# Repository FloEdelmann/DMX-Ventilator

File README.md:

# DMX-Ventilator

## Motivation

Wir waren im Dezember 2015 auf dem [Contact Indoor Festival München](https://www.facebook.com/events/544198745721461/ "Facebook-Versnataltung"). Was uns dort neben der Musik am meisten beeindruckt hat, waren die Ventilatoren, die als Effektgeräte hinter der Bühne im Zenith&nbsp;I heruntergelassen werden und sich drehen konnten. Die Flügel haben in einer einstellbaren Farbe geleuchtet und auch die Geschwindigkeit war in einem weiten Bereich regelbar.

Auf YouTube gibt es sie auch in Bewegung zu sehen:
https://www.youtube.com/watch?v=OpufAzwtyVI (rot in verschiedenen Geschwindigkeiten)
https://www.youtube.com/watch?v=SzctCUNd09I (blau)

So etwas wollten wir jetzt auch auch!

## Planung

### Elektronik

Bei der Suche nach DMX-Selbstbau-Projekten verweist letztendlich fast jede Quelle auf [Hendrik Hölschers Seiten](http://www.hoelscher-hi.de/hendrik/wahl.htm). Sein [DMX-LED-Dimmer](http://www.hoelscher-hi.de/hendrik/light/dmxled.htm) hat schon einige Features, die auch unser Ventilator haben soll: Über DMX können 8 Kanäle gesteuert werden (zusätzlich sogar gestrobed), dank AVR-Microcontroller ist die Schaltung einfach zu programmieren und zu verändern und die Hardware ist sehr modular gehalten, sodass auch andere Projekte einfach realisiert werden können.

Es fehlt jedoch die Ansteuerung eines Motors. Außerdem wollen wir LED-Strips verwenden, da sie einfach zu montieren sind, und die brauchen noch eine extra Stromversorgung. Also muss eine zweite Platine her, die die Ansteuerungen übernimmt. Sie ist so gelayoutet, dass auch ein Lochraster-Aufbau möglich ist.

Beide Schaltungen hängen dann zusammen an einer 12V-<abbr title="Gleichspannung">DC</abbr>-Stromversorgung und werden über die 8-polige Steckerleiste miteinander verbunden.

Zum Programmieren des Microcontrollers werden über den ISP-Port die nötigen Anschlüsse herausgeführt. Da es jedoch ein standardisiertes 10-Pin-ISP-Interface gibt, das auch die gängigen [Programmieradapter](http://www.mikrocontroller.net/articles/AVR_In_System_Programmer) verwenden, habe ich mir ein zusätzliches Adapterkabel gebaut.

**Downloads für [EAGLE](http://www.cadsoft.de/download-eagle/):** [avr-adapter.sch](eagle/avr-adapter.sch), [dmx-transciever.sch](eagle/dmx-transciever.sch), [motortreiber.brd](eagle/motortreiber.brd), [motortreiber.sch](eagle/motortreiber.sch)

### Gehäuse & Mechanik

Am Motor wird eine Edelstahlwelle befestigt, die von einem Kugellager drehbar in Position gehalten wird. Die Rotorblätter sollen aus milchigem Plexiglas geschnitten werden, da diese als Lichtleiter bei der Anstrahlung mit den LED-Strips hoffentlich eine gute Ausleuchtung erzielen. Sie werden zwischen zwei großen Beilagscheiben mit mehreren Schrauben / Nieten befestigt und als ganzes von vorne an die Achse geschraubt.

Mit [Autodesk 123D Design](http://www.123dapp.com/design) lässt sich recht schnell ein vorzeigbares 3D-Modell erstellen. Dabei kann man schon vor dem physischen Aufbau Mängel in der Konstruktion erkennen und beheben.

### Teile- und Bestellliste

| Stück | Bezeichnung                    | Link |
| -----:| ------------------------------ | ---- |
| 1 | 12V-DC-Getriebemotor 200rpm        | [eBay](http://www.ebay.de/itm/351368945189) |
| 1 | Neuer Motor                        | [Conrad](https://www.conrad.de/de/getriebemotor-12-v-modelcraft-rb350030-0a101r-130-227544.html) |
| 1 | RGB-LED-Strip 4m                   | [eBay](http://www.ebay.de/itm/151160889546) |
| 1 | 12V-DC-Netzteil 4A                 | [eBay](http://www.ebay.de/itm/151581215241) |
| 1 | Lochrasterplatine 4×6cm            | [eBay](http://www.ebay.de/itm/261846070281) |
| 1 | Transciever-Board                  | [embedded projects](http://shop.embedded-projects.net/sonstige/dmx-transceiver.html) |
| 1 | 3-Pol-XLR-Einbaubuchse (DMX-In)    | [Pollin](http://www.pollin.de/shop/dt/NTM2OTQ1OTk-/HiFi_Car_HiFi_Video_TV/Steckverbinder/Sonstiges/XLR_Einbaubuchse.html) |
| 1 | 3-Pol-XLR-Einbaustecker (DMX-Out)  | [Pollin](http://www.pollin.de/shop/dt/NDM2OTQ1OTk-/HiFi_Car_HiFi_Video_TV/Steckverbinder/Sonstiges/XLR_Einbaustecker.html) |
|   | mehradriges Kabel (z.B. IDE-Kabel) | |
| 1 | Edelstahlwelle 50mm, ø 20mm        | [eBay](http://www.ebay.de/itm/121103784726) |
| 1 | Flanschlager ø 20mm                | [eBay](http://www.ebay.de/itm/251852780407) |
|   | Acrylglas, 6mm                     | [eBay](http://www.ebay.de/itm/151269316675) |
|   | Aluminium-Platte, 4mm              | [eBay](http://www.ebay.de/itm/141345316955) |
|   | Holz (Multiplex), 16mm             | |
|   | MDF, 4mm                           | |
|   | Senkkopf-Holzschrauben             | |
| 6 | Rundkopf-Holzschrauben             | |
| 1 | Madenschraube M4                   | |
| 1 | Metallschraube M8, 35mm            | |
| 2 | Metallschraube M10, 30mm           | |
| 2 | Mutter M10                         | |
| 4 | Senkkopf-Metallschraube M2.5, 10mm | |
| 3 | Abstandshalter ca. 5mm             | |
| 3 | Abstandshalter ca. 12mm            | |

**Bestückung**

| Stück | Bezeichnung   | Teilenamen Transciever / Motortreiber | Link |
| -----:| ------------- | ------------------------------------- | ---- |
| 1 | 10-Pol-DIP-Switch | SW1 / –                | [eBay](http://www.ebay.de/itm/121855976441) |
| 1 | ATmega8515-P      | IC1 / –                | [eBay](http://www.ebay.de/itm/310716403642) |
| 1 | 75176AP           | IC2 / –                | [eBay](http://www.ebay.de/itm/381374573295) |
| 1 | 7805              | IC3 / –                | [Pollin](http://www.pollin.de/shop/dt/ODU5OTI4OTk-/Bauelemente_Bauteile/Aktive_Bauelemente/Spannungsregler/Spannungsregler_ST_L7805CV.html) |
| 1 | IC-Sockel 40-polig | für IC1 / –            | [Pollin](http://www.pollin.de/shop/dt/OTY5OTk1OTk-/Bauelemente_Bauteile/Mechanische_Bauelemente/IC_Fassungen_Adapterplatinen/IC_Fassung_40_polig.html) |
| 1 | IC-Sockel 8-polig | für IC2 / –            | [Pollin](http://www.pollin.de/shop/dt/Nzc5OTk1OTk-/Bauelemente_Bauteile/Mechanische_Bauelemente/IC_Fassungen_Adapterplatinen/IC_Praezisionsfassung_8_polig.html) |
| 3 | TLE-4202-B        | – / IC1, IC2, IC3      | [Pollin](http://www.pollin.de/shop/dt/NTU5ODk4OTk-/Bauelemente_Bauteile/Aktive_Bauelemente/IC/TLE4202B_STS_B57928.html) |
| 1 | Quartz 8MHz       | Q1 / –                 | [Pollin](http://www.pollin.de/shop/dt/MTk5OTY3OTk-/Bauelemente_Bauteile/Passive_Bauelemente/Quarze_Oszillatoren/Quarz.html) |
| 2 | Kondensator 27pF<br />(**genau!**) | C1, C2 / – | [Conrad](https://www.conrad.de/de/keramik-scheibenkondensator-27-pf-100-vdc-5-x-h-35-mm-x-4-mm-1-st-457175.html) |
| 2 | Kondensator 100nF | C7 / C4                | [Pollin](http://www.pollin.de/shop/dt/OTA4OTk3OTk-/Bauelemente_Bauteile/Passive_Bauelemente/Kondensatoren/Folien_Kondensator_100_nF.html) |
| 5 | Kondensator 220nF | – / C1, C2, C3, C6, C7 | [Pollin](http://www.pollin.de/shop/dt/OTgzOTk3OTk-/Bauelemente_Bauteile/Passive_Bauelemente/Kondensatoren/MKT_Kondensator.html) |
| 3 | Elko 100µF        | C5, C6 / C5            | [Pollin](http://www.pollin.de/shop/dt/MTM2OTg3OTk-/Bauelemente_Bauteile/Passive_Bauelemente/Elkos_Goldcaps/Elko_100_F_25_V_10_Stueck_NIPPON_CHEMI_CON_KZE.html) |
| 1 | LED rot 3mm       | LED1 / –               | [Pollin](http://www.pollin.de/shop/dt/MjY5OTc4OTk-/Bauelemente_Bauteile/Aktive_Bauelemente/LEDs/LED.html) |
| 1 | LED grün 3mm      | LED2 / –               | [Pollin](http://www.pollin.de/shop/dt/OTA5ODc4OTk-/Bauelemente_Bauteile/Aktive_Bauelemente/LEDs/LED_KINGBRIGHT_L_934SGDLK_gruen_3_mm_10_Stueck.html) |
| 1 | Poti 10kΩ         | R1 / –                 | [Pollin](http://www.pollin.de/shop/dt/MTM3OTU3OTk-/Bauelemente_Bauteile/Passive_Bauelemente/Potis_Trimmer_Encoder/Potentiometer_PIHER_PT_10.html) |
| 2 | Widerstand 1Ω<br />(4,7Ω geht auch) | – / R1, R2 | [Pollin](http://www.pollin.de/shop/dt/MTQyOTc3OTk-/Bauelemente_Bauteile/Passive_Bauelemente/Widerstaende/Metallfilm_Widerstaende.html) |
| 3 | Widerstand 390Ω<br />(470Ω geht auch) | R2, R3, R4 / – | [Pollin](http://www.pollin.de/shop/dt/ODIyOTc3OTk-/Bauelemente_Bauteile/Passive_Bauelemente/Widerstaende/Metallfilm_Widerstaende.html) |
| 1 | Stiftleiste 1×2   | JP4 / –                | [Pollin](http://www.pollin.de/shop/dt/OTQ0ODQ1OTk-/Bauelemente_Bauteile/Mechanische_Bauelemente/Steckverbinder_Klemmen/Stiftleiste_vergoldet_1x_20_polig_10_Stueck.html) (rowspan=5) |
| 2 | Stiftleiste 1×3   | JP2, JP3 / –           | |
| 1 | Stiftleiste 1×4   | – / JP2                | |
| 1 | Stiftleiste 1×5   | JP1 / –                | |
| 2 | Stiftleiste 1×8   | JP6 / JP1              | |
| 1 | Stiftleiste 2×3   | JP5 / –                | [Pollin](http://www.pollin.de/shop/dt/NDkyOTQ1OTk-/Bauelemente_Bauteile/Mechanische_Bauelemente/Steckverbinder_Klemmen/Stiftleiste.html) |
| 1 | Stiftbuchse 1×3   |                        | [Conrad](https://www.conrad.de/de/buchsenleiste-praezision-anzahl-reihen-1-polzahl-je-reihe-36-w-p-products-153-036-1-50-10-1-st-736427.html) (rowspan=4) |
| 1 | Stiftbuchse 1×4   |                        | |
| 1 | Stiftbuchse 1×2   |                        | |
| 2 | Stiftbuchse 1×8   |                        | |

## Aufbau der Elektronik

## TODO: Verbindungskabel falsch rum

## Programmieren

Der folgende Abschnitt bezieht sich auf das Programmieren unter Ubuntu Linux. Bei anderen Betriebssystemen müssen entsprechend andere Programme zum Assemblieren und Übertragen des Codes verwendet werden.

Als Programmier-Interface verwende ich [USBasp](http://www.fischl.de/usbasp/), das es als fertige Platine oder als Bausatz zum Selberlöten gibt. Nach Anschluss des Programmieradapters (siehe Foto oben) kann mit dem folgenden Befehl das Testfile von Hendrik Hölschers Webseite ([board.hex](http://www.hoelscher-hi.de/hendrik/light/ressources/board.hex)) übertragen werden:

    sudo avrdude -p atmega8515 -c usbasp -B 3 -U flash:w:board.hex

* `sudo`: ohne Root-Rechte bekomme ich eine Fehlermeldung (*access denied*)
* `-p atmega8515`: Angabe des verwendeten Microcontrollers
* `-c usbasp`: Angabe des Programmier-Interfaces
* `-B 3`: kleinster Wert für die `bit clock period`, damit USBasp erkannt wird
* `-U flash:w:board.hex`: schreibe das Testfile in den Flash-Speicher

**Testfunktionen:**

| DIP-Switch    | Bedeutung |
| ------------- | --------- |
| Alle DIPs off | Blinken der roten LED zeigt an, dass das Testfile in den Flash geladen wurde. |
| Alle DIPs an  | Leuchten der grünen LED zeigt an, dass alle DIP-Schalter korrekt verlötet sind. |
| DIP1 an       | Leuchten der grünen LED zeigt an, dass die fuse bits angepasst wurden. |
| DIP2 an       | Leuchtet die grüne LED, liegt ein korrektes DMX-Signal an. Ein Blinken indiziert, dass D+ und D- verpolt sind. |
| DIP3 an       | Leuchtet die grüne LED, funktioniert die angeschlossene ZC-Detection. (für uns irrelevant) |

Mit dem Testprogramm habe ich festgestellt, dass alles passt, aber die Fuse bits noch nicht gesetzt wurden. Zuerst wollen wir die aktuell gesetzten Bits lesen: `sudo avrdude -p atmega8515 -c usbasp -B 3 -n` liefert `Fuses OK (E:FF, H:D9, L:E1)`. Durch Herumspielen mit dem [AVR Fuse Calculator](http://www.engbedded.com/fusecalc), bis die Werte mit denen in http://www.hoelscher-hi.de/hendrik/light/ressources/an011.pdf übereinstimmen, bin ich auf den folgenden Befehl gekommen:

    sudo avrdude -p atmega8515 -c usbasp -B 3 -U lfuse:w:0x3f:m -U hfuse:w:0x9d:m

Danach lief das Testprogramm problemlos durch.

### `udev`-Regel

Um `avrdude` nicht jedes Mal mit Root-Rechten ausführen zu müssen, fügt man eine neue *udev rule* hinzu. Dazu erstellt man die Datei `/etc/udev/rules.d/60-usbasp.rules` mit dem folgenden Inhalt:

    # USBasp
    SUBSYSTEM=="usb", ATTRS{idVendor}=="16c0", ATTRS{idProduct}=="05dc", GROUP="adm", MODE="0666"

Danach wird die neue Datei mit `sudo service udev restart` eingelesen und man kann künftig `avrdude` ohne Root-Rechte zum Übertragen verwenden.

### Assembler und Makefile

Danach geht es an den eigentlichen Projekt-Code (`LED.asm` inkl. `lib_asm.asm`).

Als Assembler (der `.asm`-Dateien in übertragbare `.hex`-Dateien assembliert) verwenden wir `avra`.

Damit wir zum Assemblieren und Übertragen nicht immer zwei einzelne Befehle ausführen müssen, erstellen wir uns ein **Makefile**:

    file = LED.hex

    all: $(file)
        avrdude -p atmega8515 -c usbasp -B 3 -U flash:w:$(file)

    %.hex: %.asm
        avra -I "/usr/share/avra" $*.asm

    fuse:
        avrdude -p atmega8515 -c usbasp -B 3 -U lfuse:w:0x3f:m -U hfuse:w:0x9d:m

    test:
        avrdude -p atmega8515 -c usbasp -B 3 -U flash:w:board.hex

**Achtung:** Die Einrückung muss hier mit Tabs geschehen!

In `/usr/share/avra` liegen die Microcontroller-Definitionsdateien, also insbesondere auch `m8515def.inc`, das wir für unser Projekt brauchen. Mit der Option `-I` weisen wir `avra` an, auch in diesem Verzeichnis nach den Include-Dateien zu suchen.

Beim ersten Ausführen mit `make` gab es Fehlermeldungen, dass `avra` diese Kommentare nicht kennt: `/* … */` und `// …`. Daher habe ich sie durch `; …` ersetzt. Danach konnte ich bereits ohne Probleme assemblieren und übertragen und das Programm funktioniert tadellos.

Danach habe ich die beiden Dateien zusammengeführt, um leichter zu verstehen, was wo passiert.

Jetzt kann es an die eigenen Erweiterungen gehen!

### DIP-Switch

Die DIP-Schalter-Stellungen sollen unverändert weiterhin gelten:
**DIP1 - DIP9** stellen die DMX-Adresse dar (Bit 0 - 8 in aufsteigender Reihenfolge)
**DIP10** aktiviert den Standalone Mode, womit folgendes gilt:

| DIP-Switch | Funktion        |
| ----------:| --------------- |
|      1 - 3 | Programm        |
|      5 - 8 | Geschwindigkeit |
|          9 | Strobe          |

Die auswählbaren Programme müssen aber entsprechend angepasst bzw. durch neue ersetzt werden, damit diese die verschiedenen LED-Farben und den Motor entsprechend ansteuern. Zum Testen reichen aber erst mal die vorgegebenen.

### Standalone-Programme

Ich habe den IC2 (75176B), welcher für die Übersetzung von DMX in das vom Microcontroller verständliche USART zuständig ist, in China bestellt. Da dieser wegen der langen Lieferzeit noch nicht da ist, mache ich mich zuerst an die Standalone-Programme. Diese werden durch den [DIP-Switch](#dip-switch) bestimmt und können daher ohne anliegendes DMX-Signal getestet werden.

Ein vorgegebenes Programm (DIP2 an) sieht z.B. so aus:

    .org PAT1                   ; Lauflicht
    .dw 0b0000000001
    .dw 0b0000000010
    .dw 0b0000000100
    .dw 0b0000001000
    .dw 0b0000010000
    .dw 0b0000100000
    .dw 0b0001000000
    .dw 0b0010000000
    .dw 0b1100000000

Dabei stehen die einzelnen Zeilen für die unterschiedlichen Zustände, die ineinander übergefaded werden sollen. Das erste Bit ist nur beim letzten Zustand gesetzt, um das Ende des Programms zu kennzeichnen. Danach folgen die Werte für die Ausgänge `A` (ungenutzt), `M+`, `M-`, `R`, `G`, `B`, `P` (ungenutzt, aber aufs zweite Board herausgeführt) sowie zwei weitere nicht benutzte Ausgänge.

Der Motor dreht sich im Uhrzeigersinn, wenn `M+` und `M-` auf `0` und `1` gesetzt werden bzw. gegen den Uhrzeigersinn für `1` und `0`. Liegt an beiden Ausgängen der selbe Pegel an, dreht der Motor sich nicht.

Die LEDs sind an, wenn der entsprechende Ausgang auf *low* gesetzt wird.

Das folgende Beispiel zeigt also einen RGB-Fader, bei dem der Motor immer im Uhrzeigersinn dreht:

<pre>
.dw 0b0<span style="color:#aaa">0</span><span style="color:#d80">01</span><span style="color:red">0</span>11<span style="color:#aaa">000</span>
.dw 0b0<span style="color:#aaa">0</span><span style="color:#d80">01</span><span style="color:red">0</span><span style="color:#0c0">0</span>1<span style="color:#aaa">000</span>
.dw 0b0<span style="color:#aaa">0</span><span style="color:#d80">01</span>1<span style="color:#0c0">0</span>1<span style="color:#aaa">000</span>
.dw 0b0<span style="color:#aaa">0</span><span style="color:#d80">01</span>1<span style="color:#0c0">0</span><span style="color:#00f">0</span><span style="color:#aaa">000</span>
.dw 0b0<span style="color:#aaa">0</span><span style="color:#d80">01</span>11<span style="color:#00f">0</span><span style="color:#aaa">000</span>
.dw 0b<strong>1</strong><span style="color:#aaa">0</span><span style="color:#d80">01</span><span style="color:red">0</span>1<span style="color:#00f">0</span><span style="color:#aaa">000</span>
</pre>

Die anderen Programme könnt ihr im Code selbst anschauen.

### DMX-Channels

Die DMX-Channels sollen wie folgt aussehen:

| DMX-Channel | Funktion                              |
| -----------:| ------------------------------------------------------------------------ |
|           0 | <p>Motor</p><table><tbody><tr><td align="right">0 - 3</td><td>aus</td></tr><tr><td align="right">4 - 119</td><td>gegen den Uhrzeigersinn (immer langsamer)</td></tr><tr><td align="right">120 - 139</td><td>aus (Mitte)</td></tr><tr><td align="right">140 - 255</td><td>im Uhrzeigersinn (immer schneller)</td></tr></tbody></table> |
|           1 | rote LEDs                             |
|           2 | grüne LEDs                            |
|           3 | blaue LEDs                            |
|           4 | LED-Strobe (optional)                 |
|           5 | Master-Helligkeit für LEDs (optional) |

Mehr Channels brauchen wir nicht.

Um die Farb-Channels schon einmal richtig zu mappen, habe ich im Label `pwm_exit` den Abschnitt angepasst, der die Werte vom `DMX_FIELD` auf das `PWM_FIELD` kopiert, von wo aus sie im nächsten Timer-Durchlauf ausgegeben werden.

Der Motor erfordert etwas mehr Aufwand, da von einem Channel aus zwei Ausgänge gesteuert werden sollen. Ich habe mir die Funktion `eval_strobe_freq` zum Vorbild genommen und auch von der main loop aus die neue Funktion `eval_motor_speed` aufgerufen. Diese springt je nach DMX-Wert in verschiedene Sublabels. Von dort aus wird der DMX-Wert auf einen Bereich von 0 bis 115 gebracht und mit diesem Wert aus `MOTOR_MAP` der jeweils auszugebene PWM-Wert (0 bis 255) geholt und ins `PWM_FIELD` geschrieben. Das ist nötig, da wir leider nicht einfach mit einer Fließkommazahl multiplizieren können (etwa `y = x * 255/115;`).

Die Strobe-Funktion war ja schon eingebaut und musste nur so angepasst werden, dass sie auf DMX-Kanal 4 statt 1 hört (einfach) und nur die LEDs und nicht den Motor flasht. Dazu habe ich im Label `pwm` den Code so geändert, dass alle Kanäle immer normal auf den jeweiligen Wert, und danach beim Blackout mit Hilfe eines logischen Oders nur die LED-Kanäle auf 1 gesetzt werden.

#### Motor-Bremse

Da der Motor nicht allzu schnell von einem Wert auf einen anderen beschleunigen bzw. abbremsen sollte, habe ich die Funktion `eval_motor_speed` danach so abgeändert, dass in jedem Durchlauf der Soll-Wert (`DMX_FIELD` und `MOTOR_MAP`) und der Ist-Wert (`PWM_FIELD`) verglichen werden und der Output nur um eins inkrementiert oder dekrementiert wird.

Da das aber viel zu schnell abläuft, vergleiche ich vorher zusätzlich, dass die beiden Register `checkMotorL` und `checkMotorH` gleich null sind. Dieses Quasi-16-bit-Register wird vom Interrupt-Handler `pwm`, der bei jedem Overflow von `Timer0` aufgerufen wird, je um eins inkrementiert. Das war dann aber wiederum viel zu langsam, sodass `checkMotorH` sofort wieder auf null zurückgesetzt wird, sobald es den Wert 20 erreicht hat. Die Geschwindigkeit sieht im Testbetrieb vernünftig aus, eventuell muss an dem Wert aber noch gefeilt werden, sobald der Motor eingebaut ist.

Leider hat es unseren ersten Motor mit dem Wert von 20 zerschossen. Wir haben danach einen leistungsfähigeren besorgt, trotzdem wollten wir auf Nummer sicher gehen und haben den Wert auf 40 verdoppelt. Da dann aber das Anfahren sehr, sehr langsam ist, erlauben wir ein Inkrementieren öfter als ein Dekrementieren.

### Hilfe bei Assembler-Kommandos

Da man häufig mal nachschauen muss, was die einzelnen Assembler-Kommandos bedeuten, habe ich hier eine kleine Hilfe programmiert: Einfach Befehl oder Direktive eingeben (z.B. `jmp` oder `.equ`) und es werden Einzelheiten angezeigt.

<input type="text" id="asm-help-input" placeholder="Assembler-Hilfe" />
<div id="asm-help-output"></div>
<script type="text/javascript" src="asm-help.js"></script>

## Mechanischer Aufbau

*(readme is not complete; see rest of the repository for more information)*

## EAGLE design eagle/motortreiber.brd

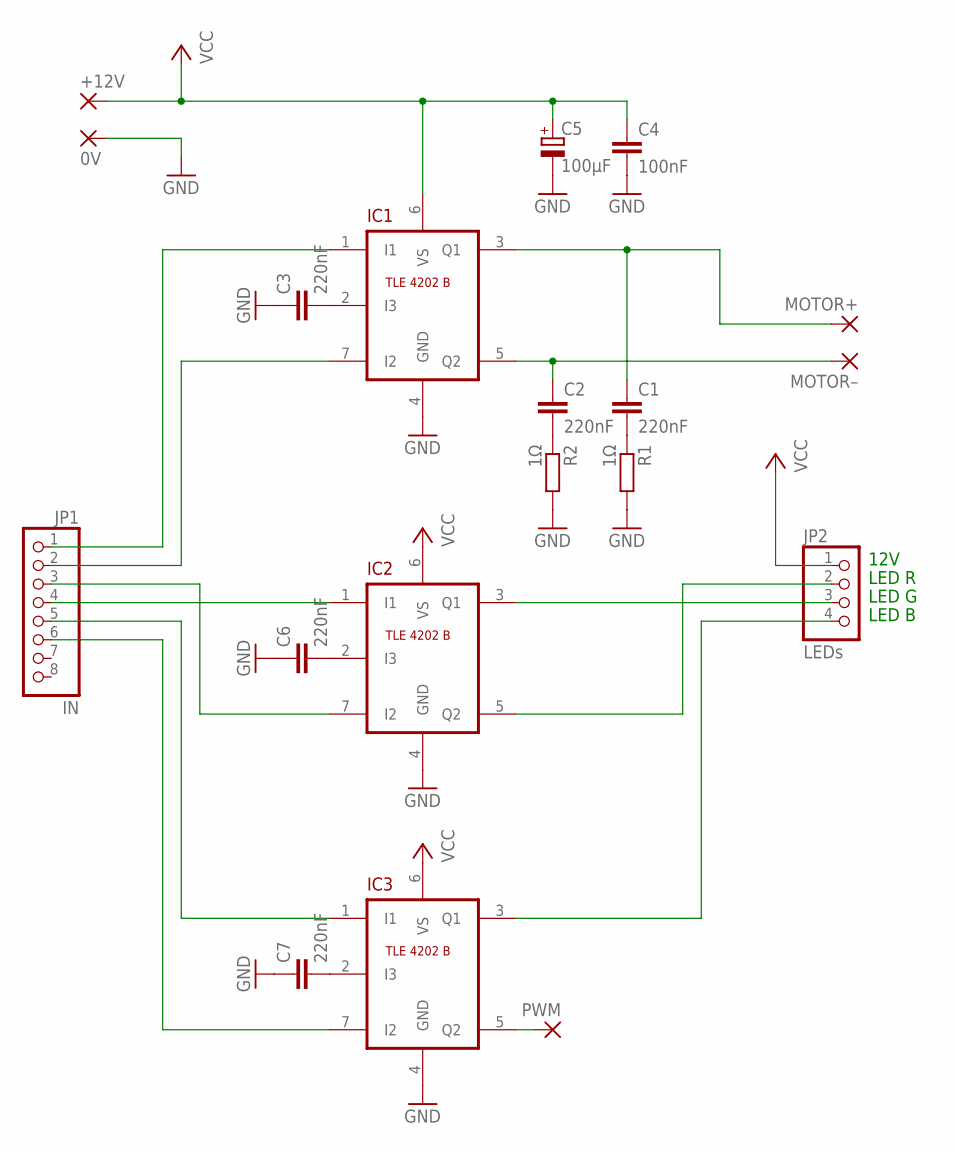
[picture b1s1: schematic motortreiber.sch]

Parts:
0V: WIREPAD2,15/1,0; 2,15/1,0
+12V: WIREPAD2,15/1,0; 2,15/1,0
C1, C2, C3, C6, C7: 220nF; C5B2.5
C4: 100nF; C2.5-3
C5: 100µF; E2,5-5
IC1, IC2, IC3: TLE-4202-B-100MIL; TO-220-7-BREADBOARD
JP1: IN; 1X08
JP2: LEDs; 1X04
MOTOR+: WIREPAD2,15/1,0; 2,15/1,0
MOTOR–: WIREPAD2,15/1,0; 2,15/1,0
PWM: WIREPAD2,15/1,0; 2,15/1,0
R1, R2: 1Ω; 0204/7

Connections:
GND: 0V.1, C3.1, C4.2, C5.-, C6.1, C7.1, IC1.4 (GND), IC2.4 (GND), IC3.4 (GND), R1.2, R2.2
unnamed: C1.1, IC1.3 (Q1), MOTOR+.1
unnamed: C2.1, IC1.5 (Q2), MOTOR–.1
unnamed: C3.2, IC1.2 (I3)
unnamed: IC1.1 (I1), JP1.1
unnamed: IC1.7 (I2), JP1.2
unnamed: C1.2, R1.1
unnamed: C2.2, R2.1
unnamed: IC2.1 (I1), JP1.4
unnamed: IC3.7 (I2), JP1.6
unnamed: IC3.1 (I1), JP1.5
unnamed: IC2.7 (I2), JP1.3
unnamed: C6.2, IC2.2 (I3)
unnamed: C7.2, IC3.2 (I3)
unnamed: IC3.5 (Q2), PWM.1
N$BOUT: IC3.3 (Q1), JP2.4
N$GOUT: IC2.3 (Q1), JP2.3
N$ROUT: IC2.5 (Q2), JP2.2
VCC: +12V.1, C4.1, C5.+, IC1.6 (VS), IC2.6 (VS), IC3.6 (VS), JP2.1

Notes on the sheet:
12V
LED R
LED G
LED B

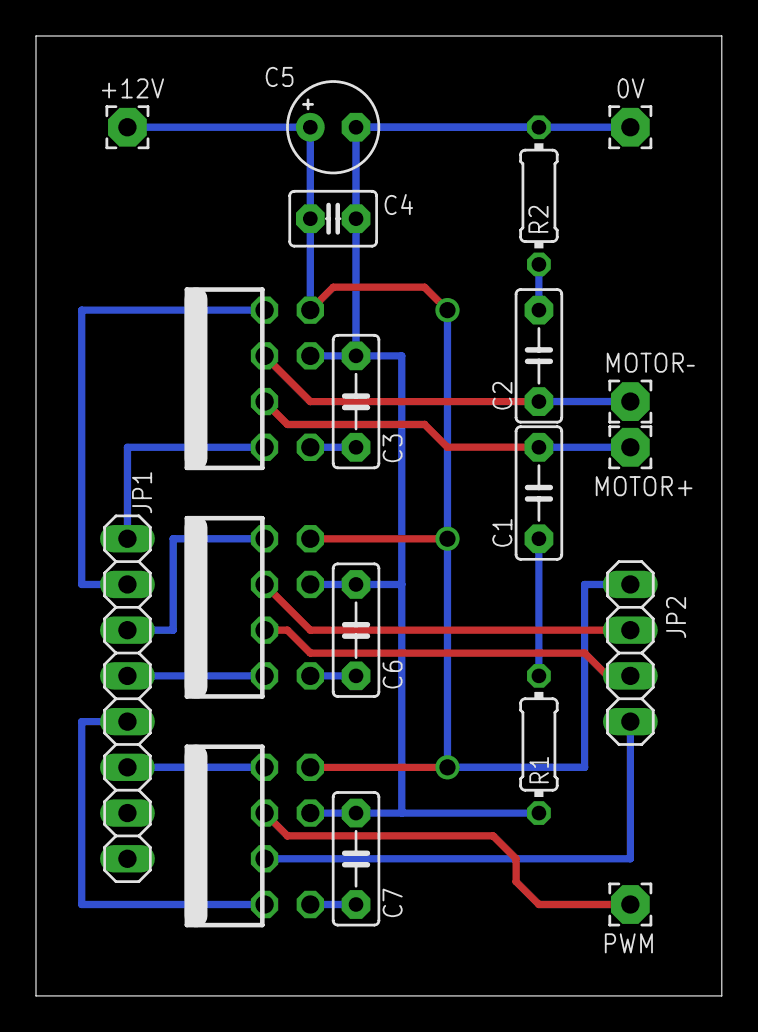
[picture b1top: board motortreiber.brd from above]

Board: 2 copper layers, 38.1 x 53.3 mm, 19 parts (0 on the bottom side), 19 nets.

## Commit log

2022-12-12 Add images
2022-12-12 Add SVG images
